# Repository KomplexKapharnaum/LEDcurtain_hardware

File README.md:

# Teensy KxKm Artnet Node Hardware
**Version: V1.5.0**
# Clément SAILLANT pour KomplexKapharnaüm

Ce projet est la partie hardware d'un nœud Artnet basé sur Teensy 4.1 pour contrôler jusqu'a 50 bandes LED. La Teensy 4.1 est un microcontrôleur puissant capable de piloter un grand nombre de LEDs. Ce projet utilise la bibliothèque FastLED et objectFLED pour contrôler les LEDs et la bibliothèque Artnet pour recevoir les données Artnet.

ce repo contient le Schéma et PCB pour la gestion jusqu'à 40 ruban led en artnet (ou autres) avec une teensy 4.1
avec gestion d'alimentation pour économiser l'énergie quand les ruban de led n'affiche rien.

code disponible ici :
https://github.com/KomplexKapharnaum/LEDcurtain/tree/main

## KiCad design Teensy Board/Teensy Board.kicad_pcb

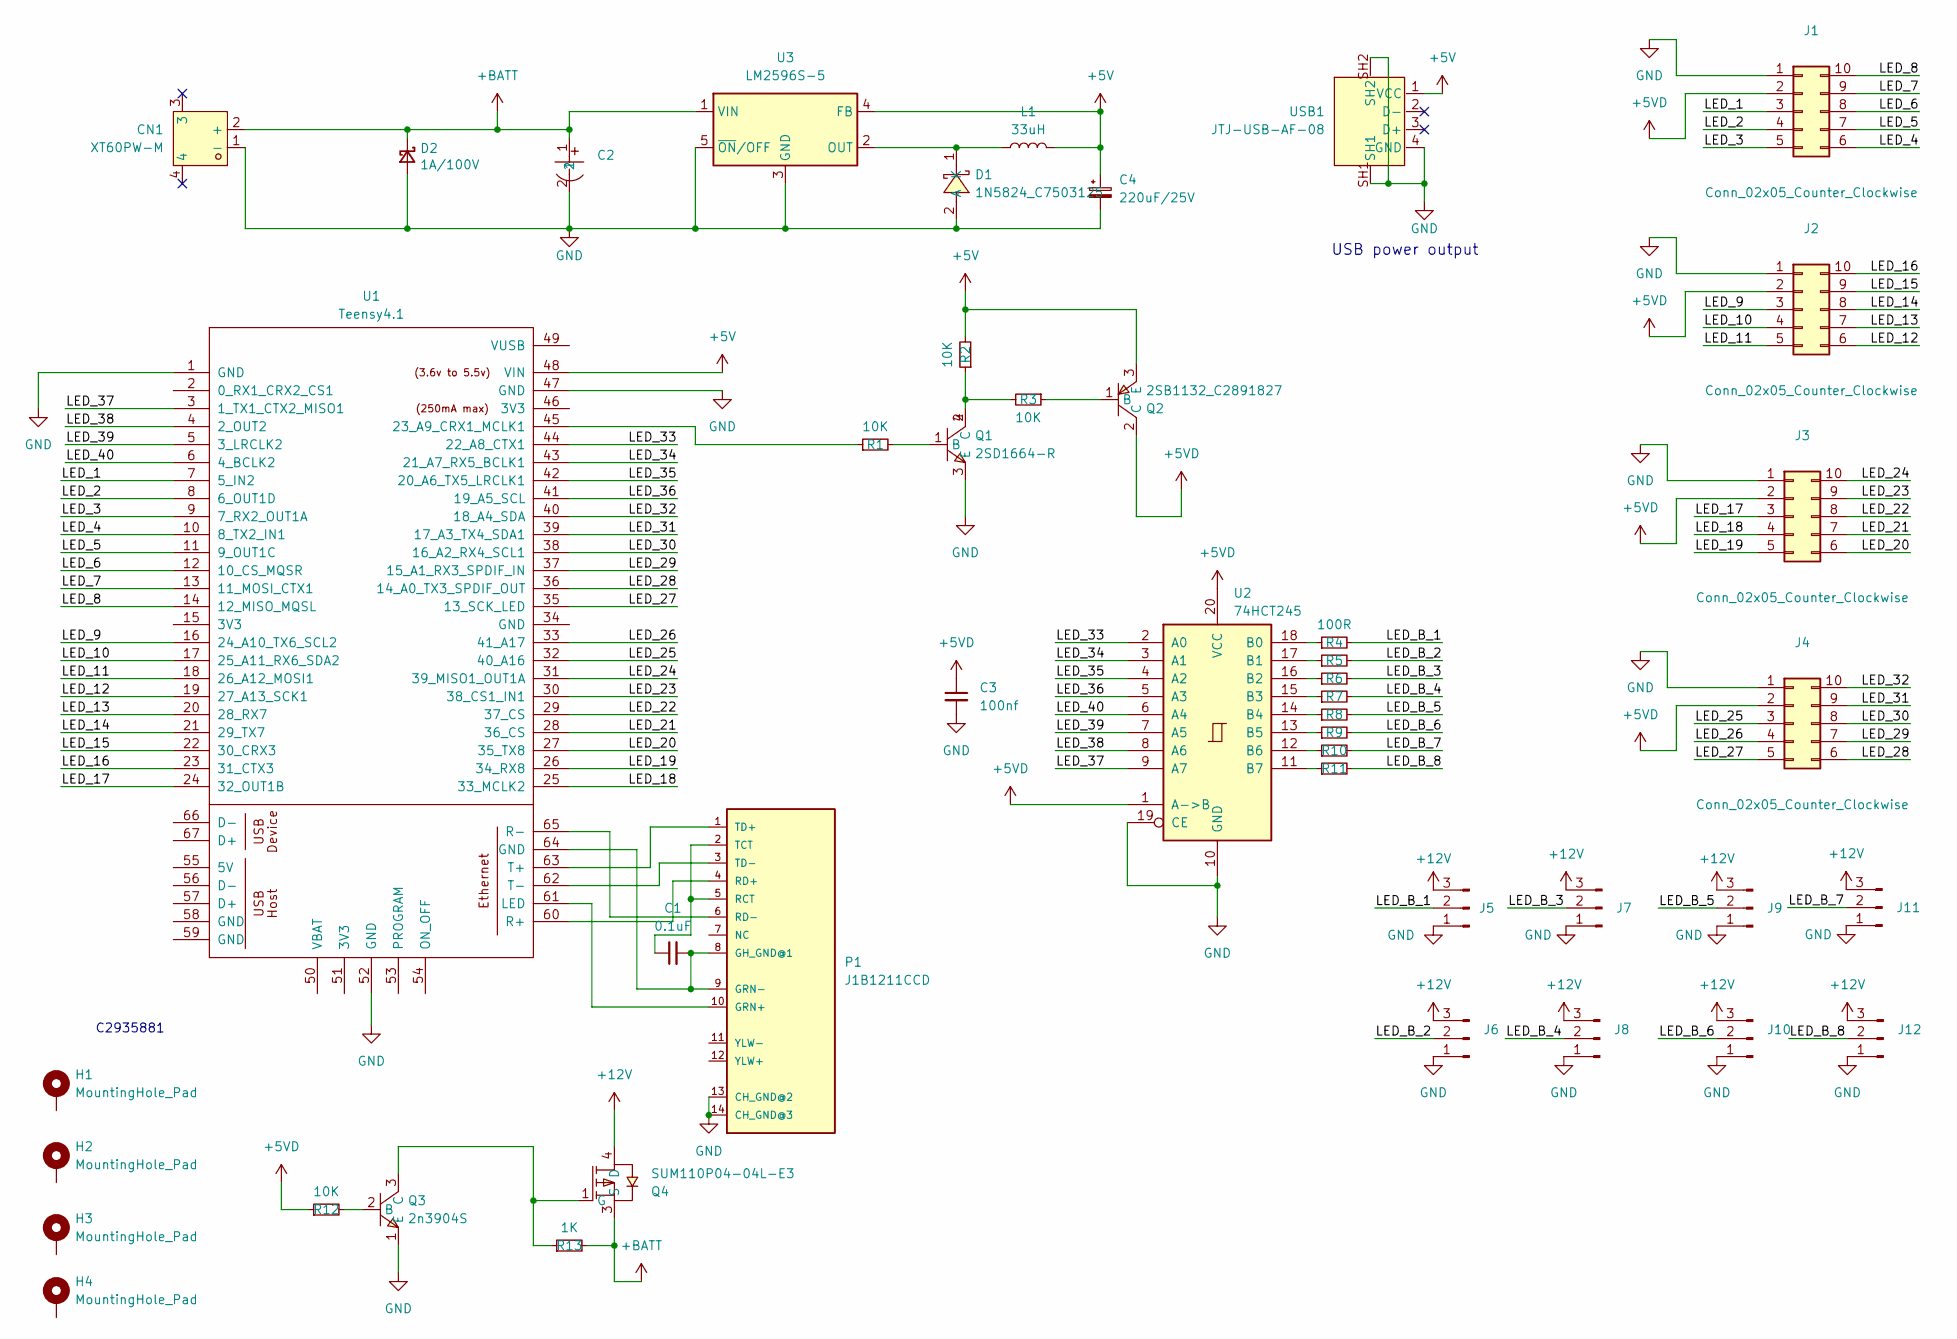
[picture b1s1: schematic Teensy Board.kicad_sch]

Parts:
C1: 0.1uF; CAP-TH_L3.8-W2.5-P2.50-D0.51; LCSC Part C575458
C2: RVT1H221M1010-C3358; CAP-SMD_BD10.0-L10.3-W10.3-LS11.3-FD; LCSC Part C3358
C3: 100nf; C_0805_2012Metric_Pad1.18x1.45mm_HandSolder; LCSC C14663
C4: 220uF/25V; CP_Elec_8x10; LCSC Part C3353
CN1: XT60PW-M; CONN-TH_XT60PW-M; LCSC Part C98732
D1: 1N5824_C7503125; DO-27_BD5.3-L8.4-P12.40-D1.3-RD; LCSC Part C7503125
D2: 1A/100V; D_SMA; LCSC C14996
H1, H2, H3, H4: MountingHole_Pad; MountingHole_3.2mm_M3_DIN965_Pad_TopOnly
J1, J2, J3, J4: Conn_02x05_Counter_Clockwise; IDC-Header_2x05_P2.54mm_Vertical
J5, J6, J7, J8, J9, J10, J11, J12: Conn_01x03_Pin; PinSocket_1x03_P2.54mm_Vertical
L1: 33uH; L_12x12mm_H6mm
P1: J1B1211CCD; RJ45-TH_J1B1211CCD; LCSC Part C910371
Q1: 2SD1664-R; SOT-89-4_L4.5-W2.5-P1.50-LS4.2-BR; LCSC Part C489328
Q2: 2SB1132_C2891827; SOT-89-3_L4.5-W2.5-P1.50-LS4.0-BR; LCSC Part C2891827
Q3: 2n3904S; SOT-23-3_L2.9-W1.3-P1.90-LS2.4-TR; LCSC Part C18536
Q4: SUM110P04-04L-E3; TO-263-2_L10.1-W9.1-P5.08-LS15.2-TL-1; LCSC Part C222440
R1, R2, R3, R12: 10K; R_0603_1608Metric
R4, R5, R6, R7, R8, R9, R10, R11: 100R; R_0603_1608Metric
R13: 1K; R_0603_1608Metric
U1: Teensy4.1; Teensy41; LCSC Part C2935881
U2: 74HCT245; TSSOP-20_4.4x6.5mm_P0.65mm
U3: LM2596S-5; TO-263-5_TabPin3
USB1: JTJ-USB-AF-08; USB-A-TH__USB-AF-90; LCSC Part C2345

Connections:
+5V: C4.1, L1.2, Q2.3 (E), R2.2, U1.48 (VIN), U3.4 (FB), USB1.1 (VCC)
+5VD: C3.1, J1.2, J2.2, J3.2, J4.2, Q2.2 (C), R12.1, U2.1 (A->B), U2.20 (VCC)
+12V: J5.3, J6.3, J7.3, J8.3, J9.3, J10.3, J11.3, J12.3, Q4.4 (D)
+BATT: C2.1, CN1.2 (+), D2.1 (K), Q4.3 (S), R13.2, U3.1 (VIN)
/LED_1: J1.3, U1.7 (5_IN2)
/LED_2: J1.4, U1.8 (6_OUT1D)
/LED_3: J1.5, U1.9 (7_RX2_OUT1A)
/LED_4: J1.6, U1.10 (8_TX2_IN1)
/LED_5: J1.7, U1.11 (9_OUT1C)
/LED_6: J1.8, U1.12 (10_CS_MQSR)
/LED_7: J1.9, U1.13 (11_MOSI_CTX1)
/LED_8: J1.10, U1.14 (12_MISO_MQSL)
/LED_9: J2.3, U1.16 (24_A10_TX6_SCL2)
/LED_10: J2.4, U1.17 (25_A11_RX6_SDA2)
/LED_11: J2.5, U1.18 (26_A12_MOSI1)
/LED_12: J2.6, U1.19 (27_A13_SCK1)
/LED_13: J2.7, U1.20 (28_RX7)
/LED_14: J2.8, U1.21 (29_TX7)
/LED_15: J2.9, U1.22 (30_CRX3)
/LED_16: J2.10, U1.23 (31_CTX3)
/LED_17: J3.3, U1.24 (32_OUT1B)
/LED_18: J3.4, U1.25 (33_MCLK2)
/LED_19: J3.5, U1.26 (34_RX8)
/LED_20: J3.6, U1.27 (35_TX8)
/LED_21: J3.7, U1.28 (36_CS)
/LED_22: J3.8, U1.29 (37_CS)
/LED_23: J3.9, U1.30 (38_CS1_IN1)
/LED_24: J3.10, U1.31 (39_MISO1_OUT1A)
/LED_25: J4.3, U1.32 (40_A16)
/LED_26: J4.4, U1.33 (41_A17)
/LED_27: J4.5, U1.35 (13_SCK_LED)
/LED_28: J4.6, U1.36 (14_A0_TX3_SPDIF_OUT)
/LED_29: J4.7, U1.37 (15_A1_RX3_SPDIF_IN)
/LED_30: J4.8, U1.38 (16_A2_RX4_SCL1)
/LED_31: J4.9, U1.39 (17_A3_TX4_SDA1)
/LED_32: J4.10, U1.40 (18_A4_SDA)
/LED_33: U1.44 (22_A8_CTX1), U2.2 (A0)
/LED_34: U1.43 (21_A7_RX5_BCLK1), U2.3 (A1)
/LED_35: U1.42 (20_A6_TX5_LRCLK1), U2.4 (A2)
/LED_36: U1.41 (19_A5_SCL), U2.5 (A3)
/LED_37: U1.3 (1_TX1_CTX2_MISO1), U2.9 (A7)
/LED_38: U1.4 (2_OUT2), U2.8 (A6)
/LED_39: U1.5 (3_LRCLK2), U2.7 (A5)
/LED_40: U1.6 (4_BCLK2), U2.6 (A4)
/LED_B_1: J5.2, R4.2
/LED_B_2: J6.2, R5.2
/LED_B_3: J7.2, R6.2
/LED_B_4: J8.2, R7.2
/LED_B_5: J9.2, R8.2
/LED_B_6: J10.2, R9.2
/LED_B_7: J11.2, R10.2
/LED_B_8: J12.2, R11.2
GND: C2.2, C3.2, C4.2, CN1.1 (-), D1.2 (A), D2.2 (A), J1.1, J2.1, J3.1, J4.1, J5.1, J6.1, J7.1, J8.1, J9.1, J10.1, J11.1, J12.1, P1.13 (CH_GND@2), P1.14 (CH_GND@3), Q1.3 (E), Q3.1 (E), U1.1 (GND), U1.47 (GND), U1.52 (GND), U2.10 (GND), U2.19 (CE), U3.3 (GND), U3.5 (~ON/OFF), USB1.4 (GND), USB1.SH1, USB1.SH2
unnamed: D1.1 (K), L1.1, U3.2 (OUT)
unnamed: C1.2, P1.8 (GH_GND@1), P1.9 (GRN-), U1.64 (GND)
unnamed: P1.10 (GRN+), U1.61 (LED)
unnamed: C1.1, P1.2 (TCT), P1.5 (RCT)
unnamed: P1.4 (RD+), U1.60 (R+)
unnamed: P1.6 (RD-), U1.65 (R-)
unnamed: P1.1 (TD+), U1.63 (T+)
unnamed: P1.3 (TD-), U1.62 (T-)
unnamed: Q1.1 (B), R1.2
unnamed: Q1.2 (C), Q1.4 (C), R2.1, R3.2
unnamed: Q2.1 (B), R3.1
unnamed: Q3.2 (B), R12.2
unnamed: Q3.3 (C), Q4.1 (G), R13.1
unnamed: R1.1, U1.45 (23_A9_CRX1_MCLK1)
unnamed: R4.1, U2.18 (B0)
unnamed: R5.1, U2.17 (B1)
unnamed: R6.1, U2.16 (B2)
unnamed: R7.1, U2.15 (B3)
unnamed: R8.1, U2.14 (B4)
unnamed: R9.1, U2.13 (B5)
unnamed: R10.1, U2.12 (B6)
unnamed: R11.1, U2.11 (B7)

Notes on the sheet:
C2935881
USB power output

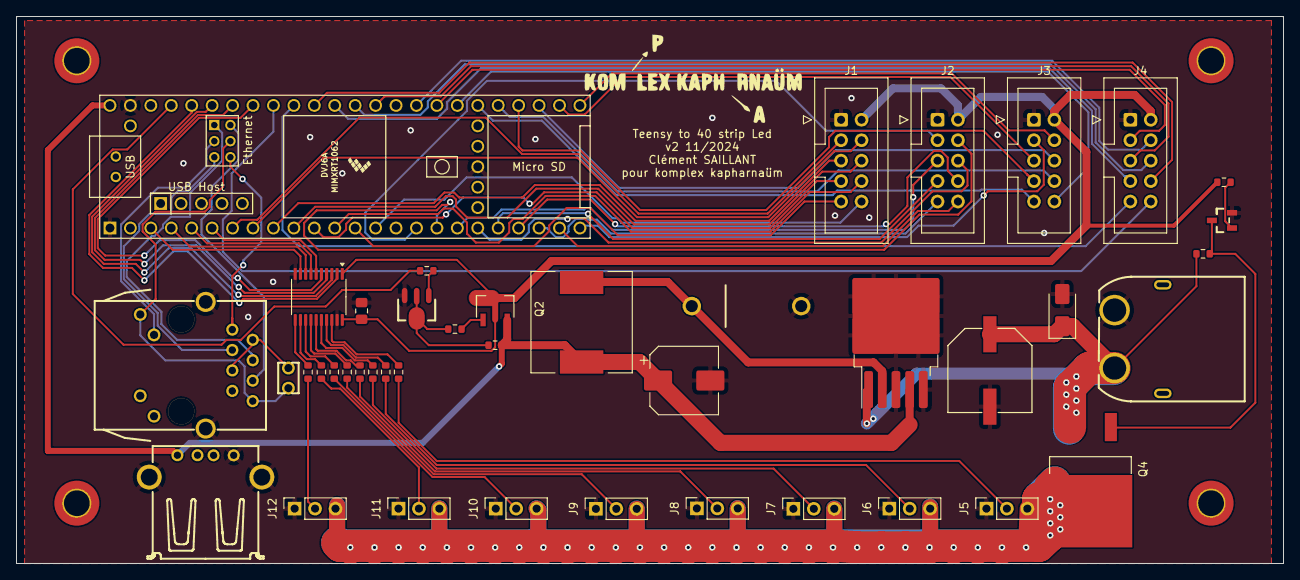
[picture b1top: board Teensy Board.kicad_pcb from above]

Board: 2 copper layers, 157.5 x 68.0 mm, 46 parts (0 on the bottom side), 75 nets.

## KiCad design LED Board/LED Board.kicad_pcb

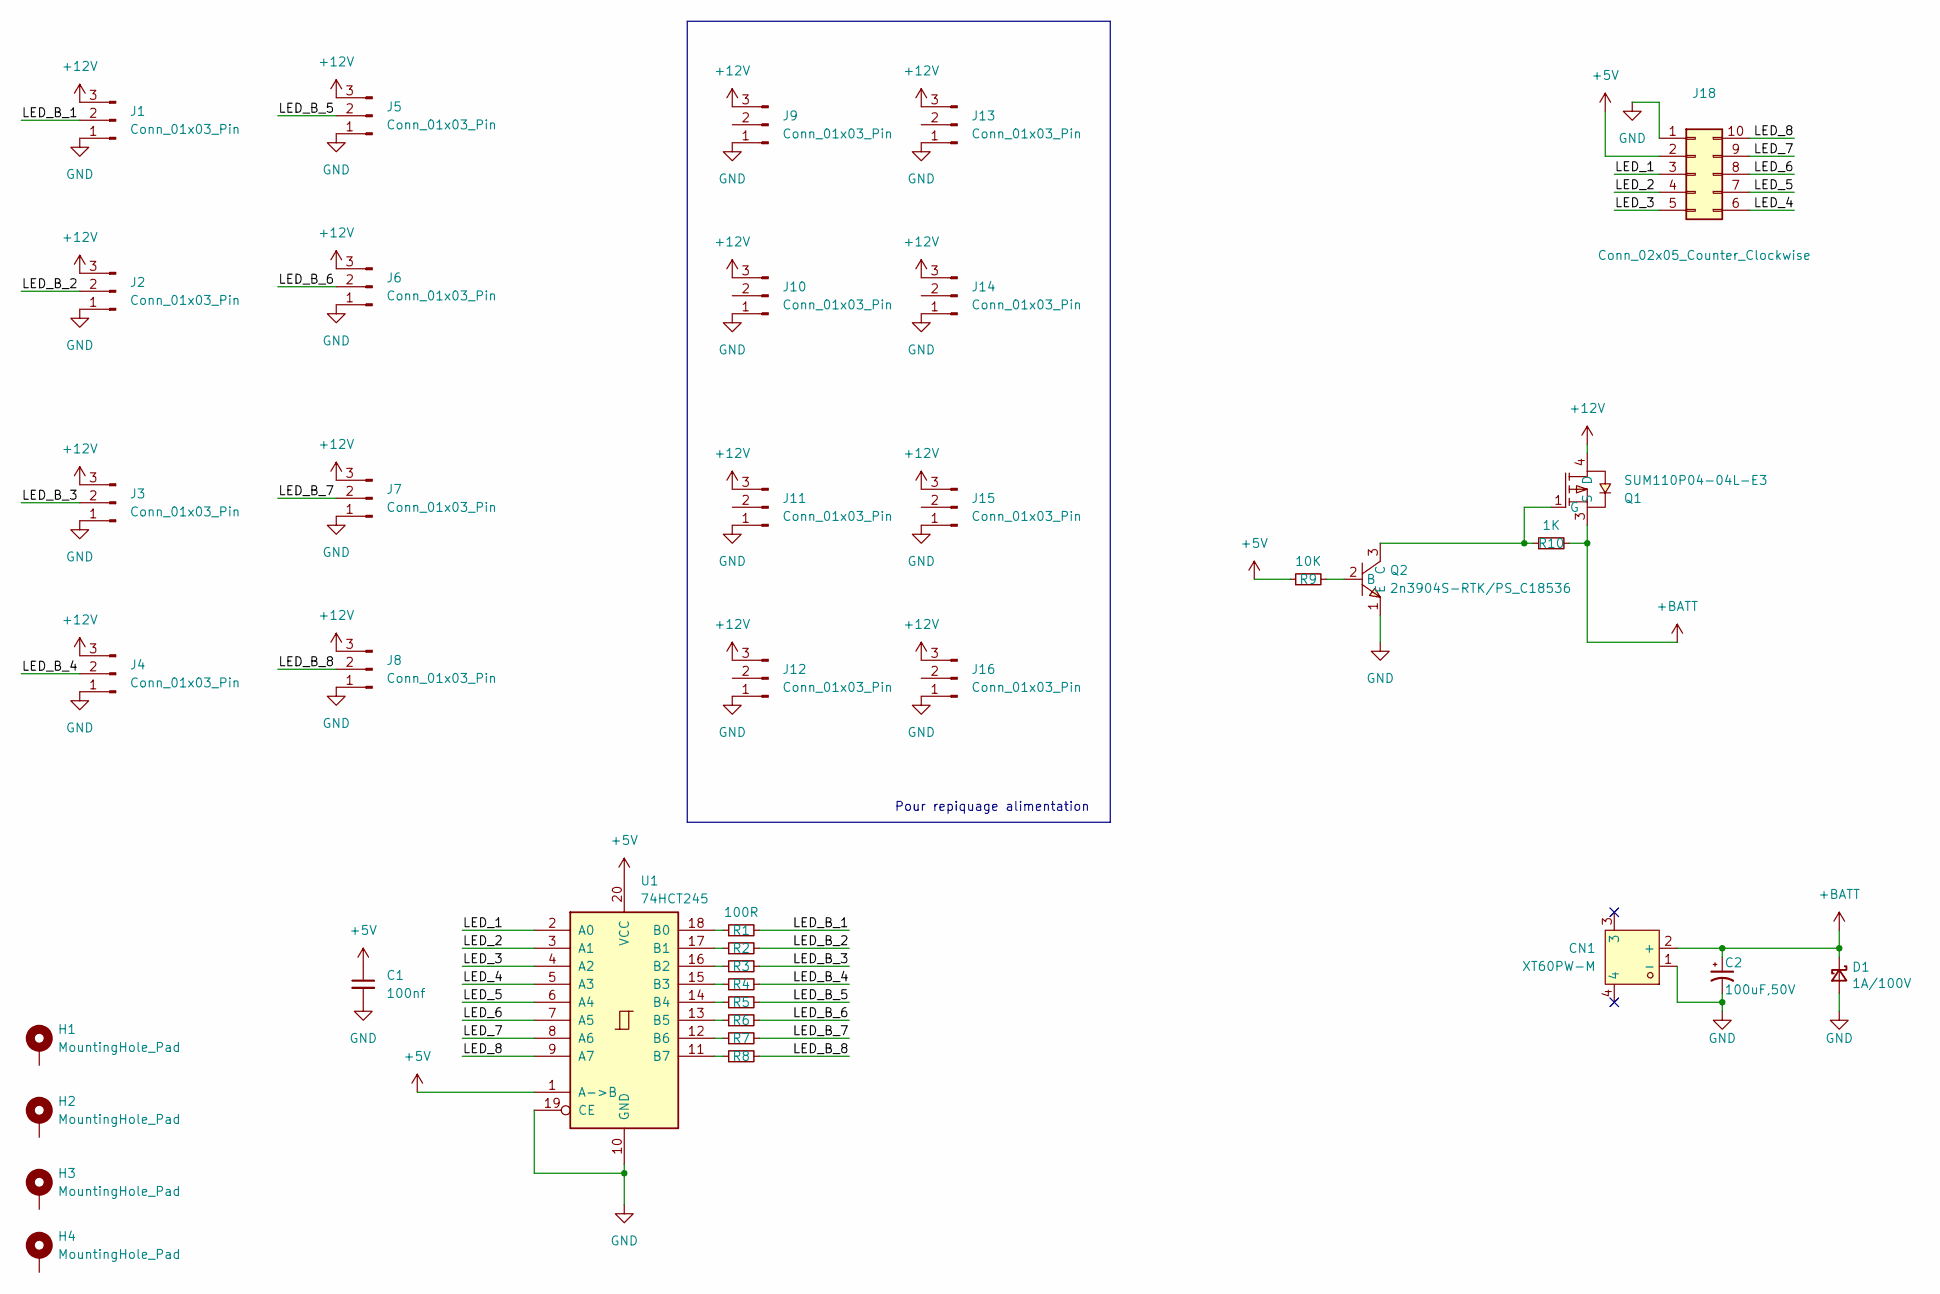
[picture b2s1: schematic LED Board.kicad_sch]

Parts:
C1: 100nf; C_0805_2012Metric_Pad1.18x1.45mm_HandSolder; LCSC C14663
C2: 100uF,50V; CP_Elec_8x10; LCSC C97812
CN1: XT60PW-M; CONN-TH_XT60PW-M; LCSC Part C98732
D1: 1A/100V; D_SMA; LCSC C14996
H1, H2, H3, H4: MountingHole_Pad; MountingHole_3.2mm_M3_DIN965_Pad_TopOnly
J1, J2, J3, J4, J5, J6, J7, J8: Conn_01x03_Pin; PinSocket_1x03_P2.54mm_Horizontal
J9, J10, J11, J12, J13, J14, J15, J16: Conn_01x03_Pin; PinSocket_1x03_P2.54mm_Vertical
J18: Conn_02x05_Counter_Clockwise; IDC-Header_2x05_P2.54mm_Vertical
Q1: SUM110P04-04L-E3; TO-263-2_L10.1-W9.1-P5.08-LS15.2-TL-1; LCSC Part C222440
Q2: 2n3904S-RTK/PS_C18536; SOT-23-3_L2.9-W1.3-P1.90-LS2.4-TR; LCSC Part C18536
R1, R2, R3, R4, R5, R6, R7, R8: 100R; R_0603_1608Metric
R9: 10K; R_0603_1608Metric
R10: 1K; R_0603_1608Metric
U1: 74HCT245; TSSOP-20_4.4x6.5mm_P0.65mm

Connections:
+5V: C1.1, J18.2, R9.1, U1.1 (A->B), U1.20 (VCC)
+12V: J1.3, J2.3, J3.3, J4.3, J5.3, J6.3, J7.3, J8.3, J9.3, J10.3, J11.3, J12.3, J13.3, J14.3, J15.3, J16.3, Q1.4 (D)
+BATT: C2.1, CN1.2 (+), D1.1 (K), Q1.3 (S), R10.2
/LED_1: J18.3, U1.2 (A0)
/LED_2: J18.4, U1.3 (A1)
/LED_3: J18.5, U1.4 (A2)
/LED_4: J18.6, U1.5 (A3)
/LED_5: J18.7, U1.6 (A4)
/LED_6: J18.8, U1.7 (A5)
/LED_7: J18.9, U1.8 (A6)
/LED_8: J18.10, U1.9 (A7)
/LED_B_1: J1.2, R1.2
/LED_B_2: J2.2, R2.2
/LED_B_3: J3.2, R3.2
/LED_B_4: J4.2, R4.2
/LED_B_5: J5.2, R5.2
/LED_B_6: J6.2, R6.2
/LED_B_7: J7.2, R7.2
/LED_B_8: J8.2, R8.2
GND: C1.2, C2.2, CN1.1 (-), D1.2 (A), J1.1, J2.1, J3.1, J4.1, J5.1, J6.1, J7.1, J8.1, J9.1, J10.1, J11.1, J12.1, J13.1, J14.1, J15.1, J16.1, J18.1, Q2.1 (E), U1.10 (GND), U1.19 (CE)
unnamed: Q1.1 (G), Q2.3 (C), R10.1
unnamed: Q2.2 (B), R9.2
unnamed: R1.1, U1.18 (B0)
unnamed: R2.1, U1.17 (B1)
unnamed: R3.1, U1.16 (B2)
unnamed: R4.1, U1.15 (B3)
unnamed: R5.1, U1.14 (B4)
unnamed: R6.1, U1.13 (B5)
unnamed: R7.1, U1.12 (B6)
unnamed: R8.1, U1.11 (B7)

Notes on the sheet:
Pour repiquage alimentation

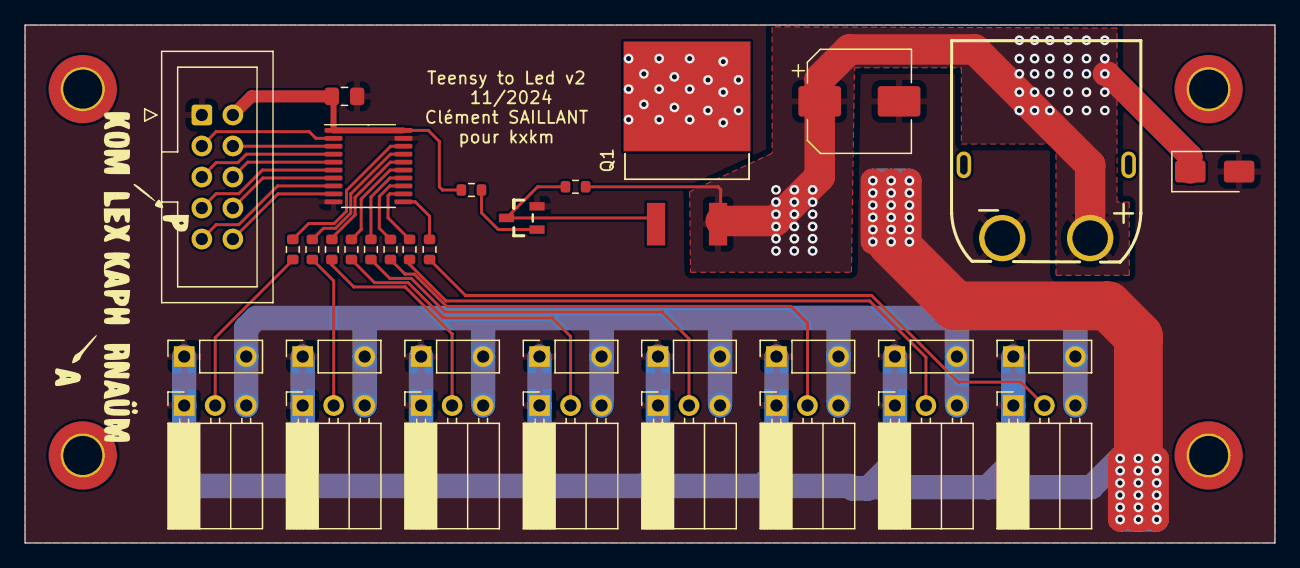
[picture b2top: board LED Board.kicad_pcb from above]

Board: 2 copper layers, 102.4 x 42.4 mm, 38 parts (0 on the bottom side), 30 nets.

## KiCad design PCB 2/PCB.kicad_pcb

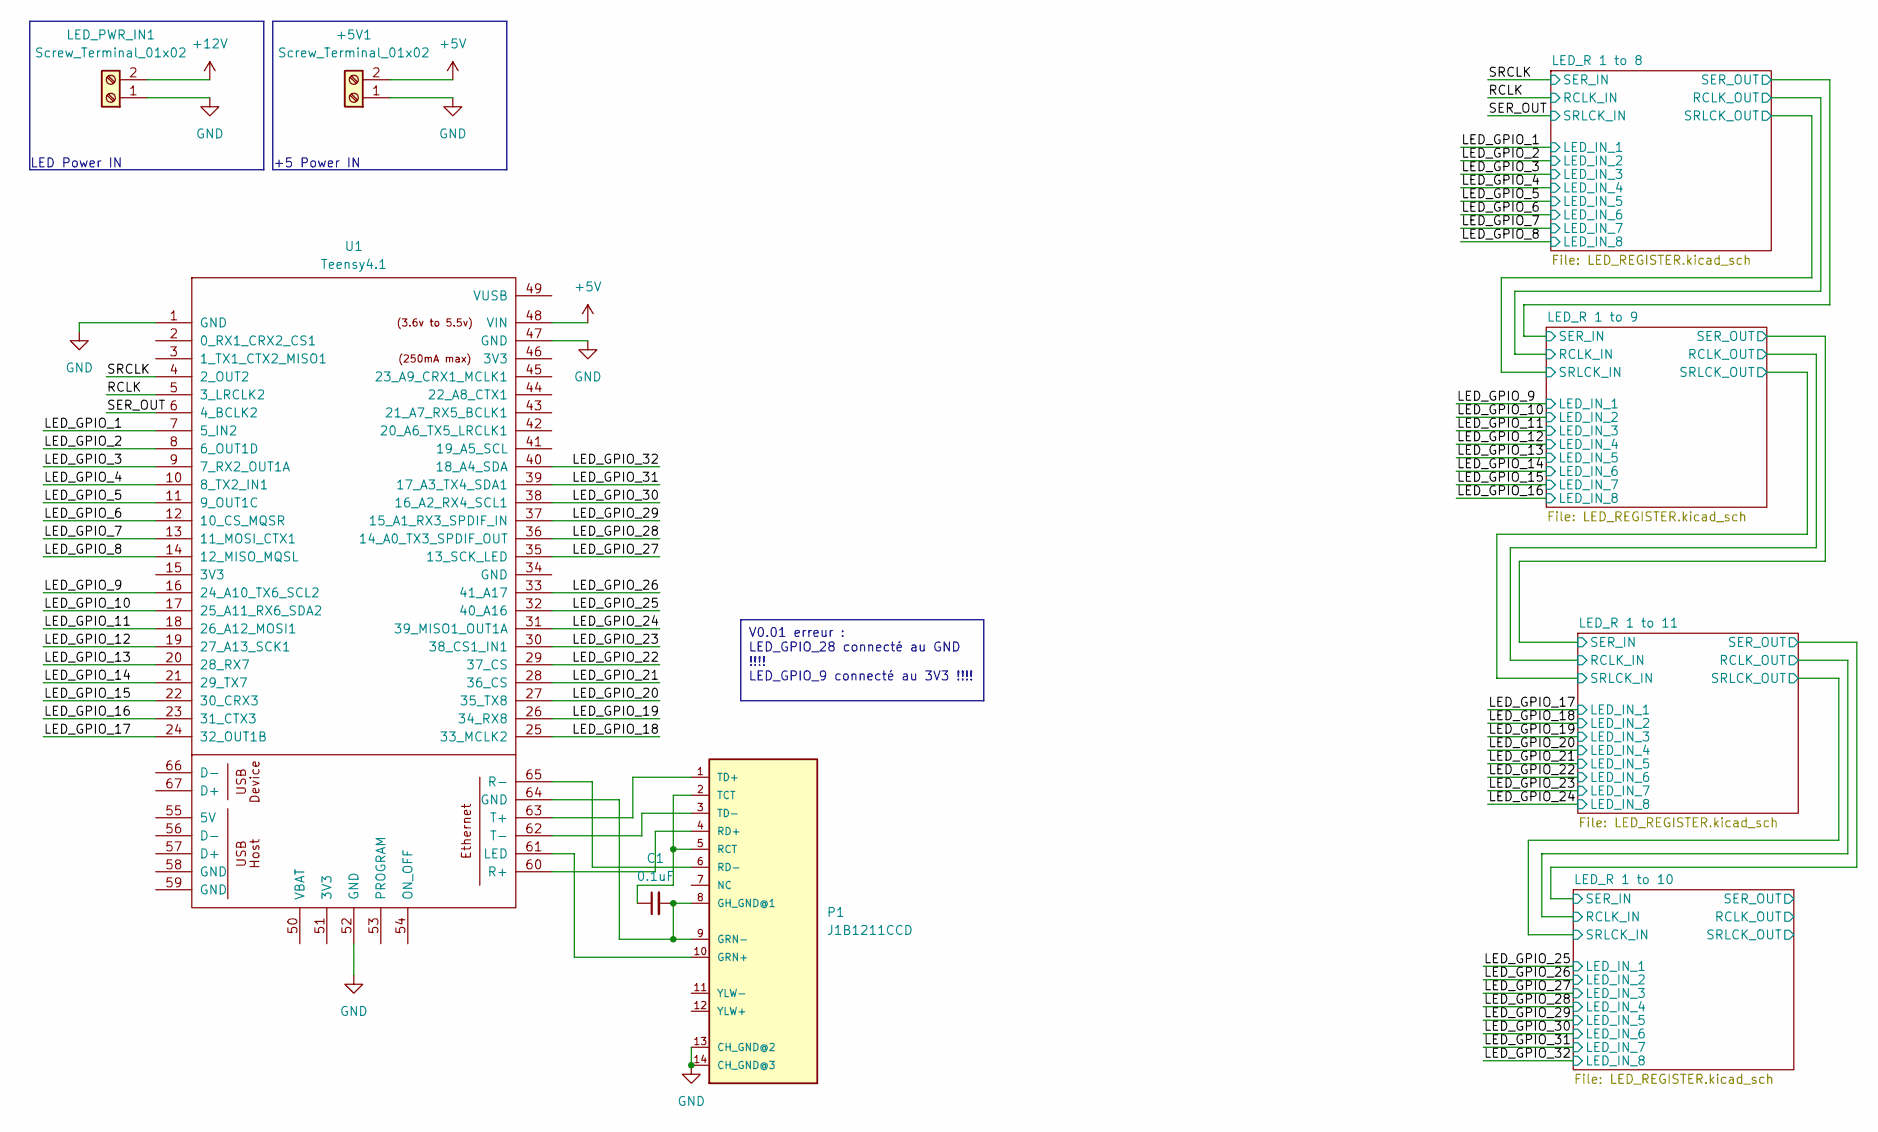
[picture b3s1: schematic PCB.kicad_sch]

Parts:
+5V1: Screw_Terminal_01x02; Wago_734-162_1x02_P3.50mm_Horizontal
C1: 0.1uF; C_Disc_D3.0mm_W1.6mm_P2.50mm
LED_PWR_IN1: Screw_Terminal_01x02; SolderWire-2.5sqmm_1x02_P8.8mm_D2.4mm_OD4.4mm
P1: J1B1211CCD
U1: Teensy4.1; Teensy41

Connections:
+5V: +5V1.2, U1.48 (VIN); also elsewhere on the board
+12V: LED_PWR_IN1.2; also elsewhere on the board
/LED_GPIO_1: U1.7 (5_IN2); also elsewhere on the board
/LED_GPIO_2: U1.8 (6_OUT1D); also elsewhere on the board
/LED_GPIO_3: U1.9 (7_RX2_OUT1A); also elsewhere on the board
/LED_GPIO_4: U1.10 (8_TX2_IN1); also elsewhere on the board
/LED_GPIO_5: U1.11 (9_OUT1C); also elsewhere on the board
/LED_GPIO_6: U1.12 (10_CS_MQSR); also elsewhere on the board
/LED_GPIO_7: U1.13 (11_MOSI_CTX1); also elsewhere on the board
/LED_GPIO_8: U1.14 (12_MISO_MQSL); also elsewhere on the board
/LED_GPIO_9: U1.15 (3V3); also elsewhere on the board
/LED_GPIO_10: U1.16 (24_A10_TX6_SCL2); also elsewhere on the board
/LED_GPIO_11: U1.17 (25_A11_RX6_SDA2); also elsewhere on the board
/LED_GPIO_12: U1.18 (26_A12_MOSI1); also elsewhere on the board
/LED_GPIO_13: U1.19 (27_A13_SCK1); also elsewhere on the board
/LED_GPIO_14: U1.20 (28_RX7); also elsewhere on the board
/LED_GPIO_15: U1.21 (29_TX7); also elsewhere on the board
/LED_GPIO_16: U1.22 (30_CRX3); also elsewhere on the board
/LED_GPIO_17: U1.23 (31_CTX3); also elsewhere on the board
/LED_GPIO_18: U1.24 (32_OUT1B); also elsewhere on the board
/LED_GPIO_19: U1.25 (33_MCLK2); also elsewhere on the board
/LED_GPIO_20: U1.26 (34_RX8); also elsewhere on the board
/LED_GPIO_21: U1.27 (35_TX8); also elsewhere on the board
/LED_GPIO_22: U1.28 (36_CS); also elsewhere on the board
/LED_GPIO_23: U1.29 (37_CS); also elsewhere on the board
/LED_GPIO_24: U1.30 (38_CS1_IN1); also elsewhere on the board
/LED_GPIO_25: U1.31 (39_MISO1_OUT1A); also elsewhere on the board
/LED_GPIO_26: U1.32 (40_A16); also elsewhere on the board
/LED_GPIO_27: U1.33 (41_A17); also elsewhere on the board
/LED_GPIO_28: U1.34 (GND); also elsewhere on the board
/LED_GPIO_29: U1.36 (14_A0_TX3_SPDIF_OUT); also elsewhere on the board
/LED_GPIO_30: U1.37 (15_A1_RX3_SPDIF_IN); also elsewhere on the board
/LED_GPIO_31: U1.38 (16_A2_RX4_SCL1); also elsewhere on the board
/LED_GPIO_32: U1.39 (17_A3_TX4_SDA1); also elsewhere on the board
/RCLK: U1.5 (3_LRCLK2); also elsewhere on the board
/SER_OUT: U1.6 (4_BCLK2); also elsewhere on the board
/SRCLK: U1.4 (2_OUT2); also elsewhere on the board
GND: +5V1.1, LED_PWR_IN1.1, P1.13 (CH_GND@2), P1.14 (CH_GND@3), U1.1 (GND), U1.47 (GND), U1.52 (GND); also elsewhere on the board
unnamed: C1.2, P1.8 (GH_GND@1), P1.9 (GRN-), U1.64 (GND)
unnamed: P1.10 (GRN+), U1.61 (LED)
unnamed: C1.1, P1.2 (TCT), P1.5 (RCT)
unnamed: P1.4 (RD+), U1.60 (R+)
unnamed: P1.6 (RD-), U1.65 (R-)
unnamed: P1.1 (TD+), U1.63 (T+)
unnamed: P1.3 (TD-), U1.62 (T-)

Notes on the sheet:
V0.01 erreur : LED_GPIO_28 connecté au GND !!!! LED_GPIO_9 connecté au 3V3 !!!!
+5 Power IN
LED Power IN

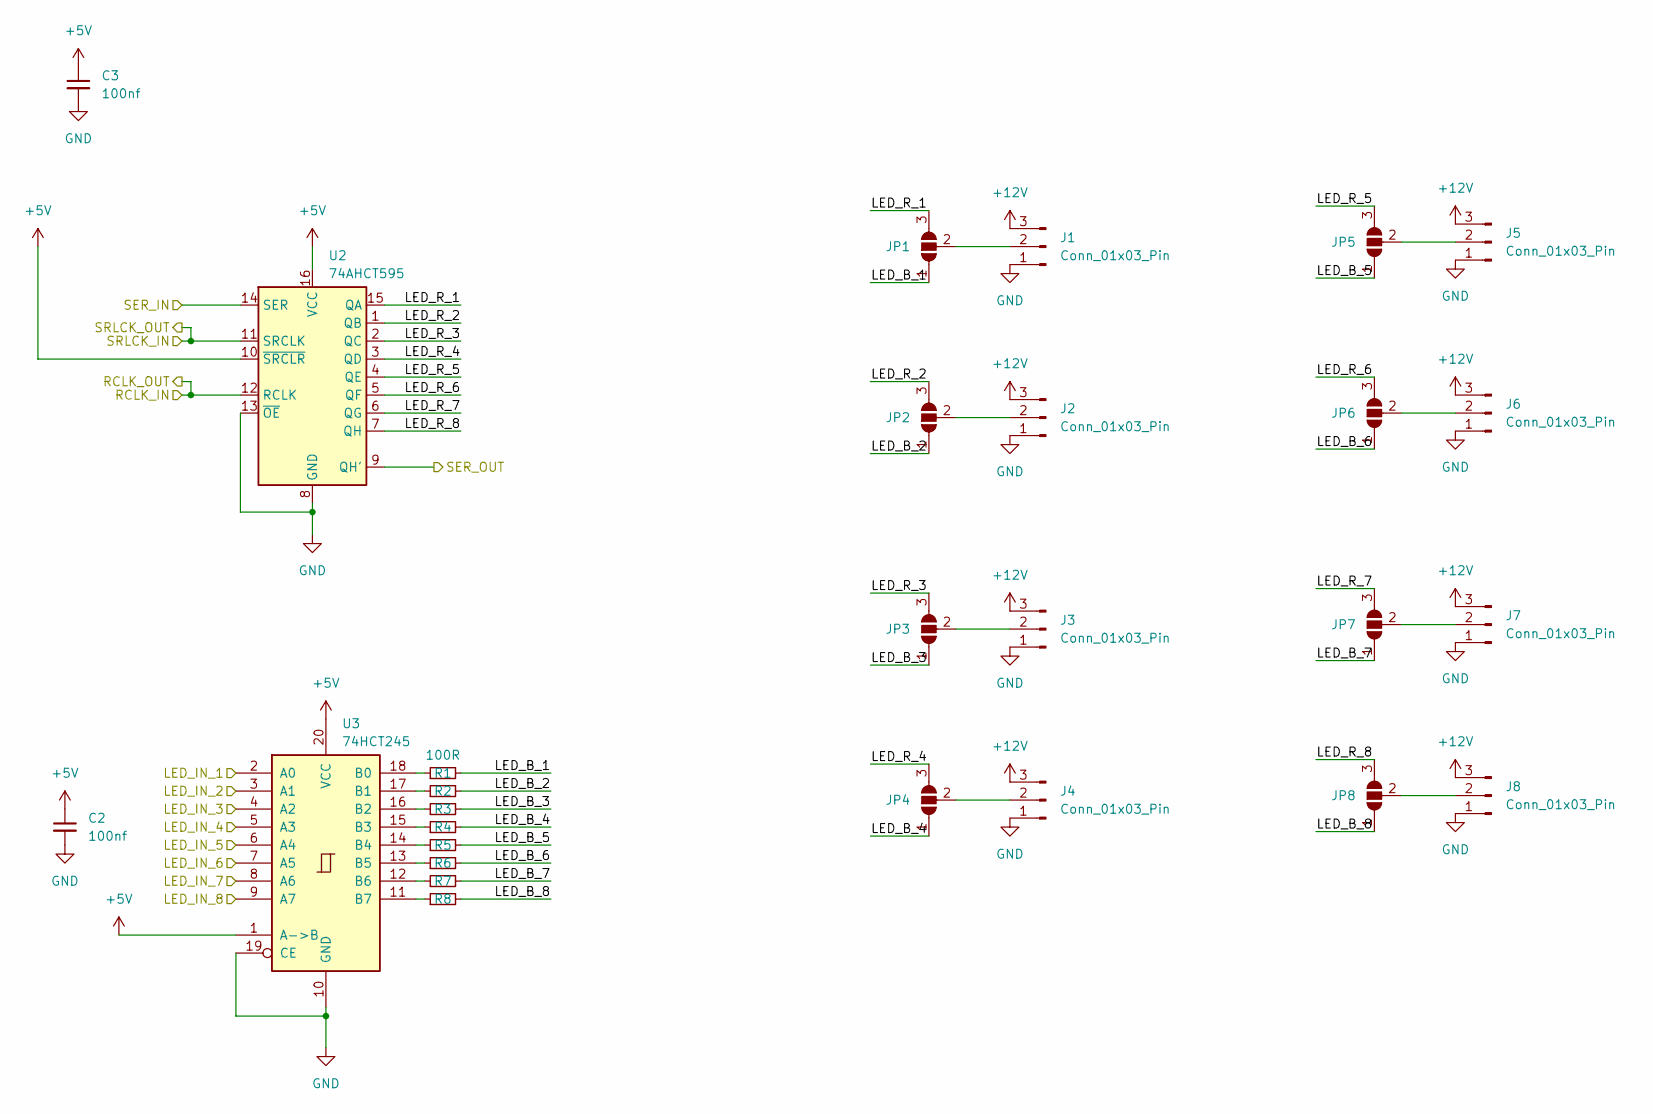
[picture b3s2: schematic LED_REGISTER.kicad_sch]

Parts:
C2, C3: 100nf; C_0805_2012Metric_Pad1.18x1.45mm_HandSolder; LCSC C14663
J1, J2, J3, J4, J5, J6, J7, J8: Conn_01x03_Pin; SolderWire-2.5sqmm_1x03_P7.2mm_D2.4mm_OD3.6mm
JP1, JP2, JP3, JP4, JP5, JP6, JP7, JP8: SolderJumper_3_Open; SolderJumper-3_P1.3mm_Open_RoundedPad1.0x1.5mm_NumberLabels
R1, R2, R3, R4, R5, R6, R7, R8: 100R; R_0201_0603Metric
U2: 74AHCT595; TSSOP-16_4.4x5mm_P0.65mm
U3: 74HCT245; TSSOP-20_4.4x6.5mm_P0.65mm

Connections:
+5V: C2.1, C3.1, U2.10 (~SRCLR), U2.16 (VCC), U3.1 (A->B), U3.20 (VCC); also elsewhere on the board
+12V: J1.3, J2.3, J3.3, J4.3, J5.3, J6.3, J7.3, J8.3; also elsewhere on the board
/LED_GPIO_1: U3.2 (A0); also elsewhere on the board
/LED_GPIO_2: U3.3 (A1); also elsewhere on the board
/LED_GPIO_3: U3.4 (A2); also elsewhere on the board
/LED_GPIO_4: U3.5 (A3); also elsewhere on the board
/LED_GPIO_5: U3.6 (A4); also elsewhere on the board
/LED_GPIO_6: U3.7 (A5); also elsewhere on the board
/LED_GPIO_7: U3.8 (A6); also elsewhere on the board
/LED_GPIO_8: U3.9 (A7); also elsewhere on the board
/LED_R 1 to 8/LED_B_1: JP1.1 (A), R1.2
/LED_R 1 to 8/LED_B_2: JP2.1 (A), R2.2
/LED_R 1 to 8/LED_B_3: JP3.1 (A), R3.2
/LED_R 1 to 8/LED_B_4: JP4.1 (A), R4.2
/LED_R 1 to 8/LED_B_5: JP5.1 (A), R5.2
/LED_R 1 to 8/LED_B_6: JP6.1 (A), R6.2
/LED_R 1 to 8/LED_B_7: JP7.1 (A), R7.2
/LED_R 1 to 8/LED_B_8: JP8.1 (A), R8.2
/LED_R 1 to 8/LED_R_1: JP1.3 (B), U2.15 (QA)
/LED_R 1 to 8/LED_R_2: JP2.3 (B), U2.1 (QB)
/LED_R 1 to 8/LED_R_3: JP3.3 (B), U2.2 (QC)
/LED_R 1 to 8/LED_R_4: JP4.3 (B), U2.3 (QD)
/LED_R 1 to 8/LED_R_5: JP5.3 (B), U2.4 (QE)
/LED_R 1 to 8/LED_R_6: JP6.3 (B), U2.5 (QF)
/LED_R 1 to 8/LED_R_7: JP7.3 (B), U2.6 (QG)
/LED_R 1 to 8/LED_R_8: JP8.3 (B), U2.7 (QH)
/LED_R 1 to 8/SER_OUT: U2.9 (QH'); also elsewhere on the board
/RCLK: U2.12 (RCLK); also elsewhere on the board
/SER_OUT: U2.11 (SRCLK); also elsewhere on the board
/SRCLK: U2.14 (SER); also elsewhere on the board
GND: C2.2, C3.2, J1.1, J2.1, J3.1, J4.1, J5.1, J6.1, J7.1, J8.1, U2.8 (GND), U2.13 (~OE), U3.10 (GND), U3.19 (CE); also elsewhere on the board
unnamed: J1.2, JP1.2 (C)
unnamed: J2.2, JP2.2 (C)
unnamed: J3.2, JP3.2 (C)
unnamed: J4.2, JP4.2 (C)
unnamed: J5.2, JP5.2 (C)
unnamed: J6.2, JP6.2 (C)
unnamed: J7.2, JP7.2 (C)
unnamed: J8.2, JP8.2 (C)
unnamed: R1.1, U3.18 (B0)
unnamed: R2.1, U3.17 (B1)
unnamed: R3.1, U3.16 (B2)
unnamed: R4.1, U3.15 (B3)
unnamed: R5.1, U3.14 (B4)
unnamed: R6.1, U3.13 (B5)
unnamed: R7.1, U3.12 (B6)
unnamed: R8.1, U3.11 (B7)

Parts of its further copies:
C4, C5, C6, C7, C8, C9: 100nf; C_0805_2012Metric_Pad1.18x1.45mm_HandSolder; LCSC C14663
J9, J10, J11, J12, J13, J14, J15, J16, J17, J18, J19, J20, J21, J22, J23, J24, J25, J26, J27, J28, J29, J30, J31, J32: Conn_01x03_Pin; SolderWire-2.5sqmm_1x03_P7.2mm_D2.4mm_OD3.6mm
JP9, JP10, JP11, JP12, JP13, JP14, JP15, JP16, JP17, JP18, JP19, JP20, JP21, JP22, JP23, JP24, JP25, JP26, JP27, JP28, JP29, JP30, JP31, JP32: SolderJumper_3_Open; SolderJumper-3_P1.3mm_Open_RoundedPad1.0x1.5mm_NumberLabels
R9, R10, R11, R12, R13, R14, R15, R16, R17, R18, R19, R20, R21, R22, R23, R24, R25, R26, R27, R28, R29, R30, R31, R32: 100R; R_0201_0603Metric
U4, U6, U8: 74AHCT595; TSSOP-16_4.4x5mm_P0.65mm
U5, U7, U9: 74HCT245; TSSOP-20_4.4x6.5mm_P0.65mm

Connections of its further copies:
+5V: C4.1, C5.1, C6.1, C7.1, C8.1, C9.1, U4.10 (~SRCLR), U4.16 (VCC), U5.1 (A->B), U5.20 (VCC), U6.10 (~SRCLR), U6.16 (VCC), U7.1 (A->B), U7.20 (VCC), U8.10 (~SRCLR), U8.16 (VCC), U9.1 (A->B), U9.20 (VCC); also elsewhere on the board
+12V: J9.3, J10.3, J11.3, J12.3, J13.3, J14.3, J15.3, J16.3, J17.3, J18.3, J19.3, J20.3, J21.3, J22.3, J23.3, J24.3, J25.3, J26.3, J27.3, J28.3, J29.3, J30.3, J31.3, J32.3; also elsewhere on the board
/LED_GPIO_9: U5.2 (A0); also elsewhere on the board
/LED_GPIO_10: U5.3 (A1); also elsewhere on the board
/LED_GPIO_11: U5.4 (A2); also elsewhere on the board
/LED_GPIO_12: U5.5 (A3); also elsewhere on the board
/LED_GPIO_13: U5.6 (A4); also elsewhere on the board
/LED_GPIO_14: U5.7 (A5); also elsewhere on the board
/LED_GPIO_15: U5.8 (A6); also elsewhere on the board
/LED_GPIO_16: U5.9 (A7); also elsewhere on the board
/LED_GPIO_17: U7.2 (A0); also elsewhere on the board
/LED_GPIO_18: U7.3 (A1); also elsewhere on the board
/LED_GPIO_19: U7.4 (A2); also elsewhere on the board
/LED_GPIO_20: U7.5 (A3); also elsewhere on the board
/LED_GPIO_21: U7.6 (A4); also elsewhere on the board
/LED_GPIO_22: U7.7 (A5); also elsewhere on the board
/LED_GPIO_23: U7.8 (A6); also elsewhere on the board
/LED_GPIO_24: U7.9 (A7); also elsewhere on the board
/LED_GPIO_25: U9.2 (A0); also elsewhere on the board
/LED_GPIO_26: U9.3 (A1); also elsewhere on the board
/LED_GPIO_27: U9.4 (A2); also elsewhere on the board
/LED_GPIO_28: U9.5 (A3); also elsewhere on the board
/LED_GPIO_29: U9.6 (A4); also elsewhere on the board
/LED_GPIO_30: U9.7 (A5); also elsewhere on the board
/LED_GPIO_31: U9.8 (A6); also elsewhere on the board
/LED_GPIO_32: U9.9 (A7); also elsewhere on the board
/LED_R 1 to 8/SER_OUT: U4.14 (SER); also elsewhere on the board
/LED_R 1 to 9/LED_B_1: JP9.1 (A), R9.2
/LED_R 1 to 9/LED_B_2: JP10.1 (A), R10.2
/LED_R 1 to 9/LED_B_3: JP11.1 (A), R11.2
/LED_R 1 to 9/LED_B_4: JP12.1 (A), R12.2
/LED_R 1 to 9/LED_B_5: JP13.1 (A), R13.2
/LED_R 1 to 9/LED_B_6: JP14.1 (A), R14.2
/LED_R 1 to 9/LED_B_7: JP15.1 (A), R15.2
/LED_R 1 to 9/LED_B_8: JP16.1 (A), R16.2
/LED_R 1 to 9/LED_R_1: JP9.3 (B), U4.15 (QA)
/LED_R 1 to 9/LED_R_2: JP10.3 (B), U4.1 (QB)
/LED_R 1 to 9/LED_R_3: JP11.3 (B), U4.2 (QC)
/LED_R 1 to 9/LED_R_4: JP12.3 (B), U4.3 (QD)
/LED_R 1 to 9/LED_R_5: JP13.3 (B), U4.4 (QE)
/LED_R 1 to 9/LED_R_6: JP14.3 (B), U4.5 (QF)
/LED_R 1 to 9/LED_R_7: JP15.3 (B), U4.6 (QG)
/LED_R 1 to 9/LED_R_8: JP16.3 (B), U4.7 (QH)
/LED_R 1 to 10/LED_B_1: JP25.1 (A), R25.2
/LED_R 1 to 10/LED_B_2: JP26.1 (A), R26.2
/LED_R 1 to 10/LED_B_3: JP27.1 (A), R27.2
/LED_R 1 to 10/LED_B_4: JP28.1 (A), R28.2
/LED_R 1 to 10/LED_B_5: JP29.1 (A), R29.2
/LED_R 1 to 10/LED_B_6: JP30.1 (A), R30.2
/LED_R 1 to 10/LED_B_7: JP31.1 (A), R31.2
/LED_R 1 to 10/LED_B_8: JP32.1 (A), R32.2
/LED_R 1 to 10/LED_R_1: JP25.3 (B), U8.15 (QA)
/LED_R 1 to 10/LED_R_2: JP26.3 (B), U8.1 (QB)
/LED_R 1 to 10/LED_R_3: JP27.3 (B), U8.2 (QC)
/LED_R 1 to 10/LED_R_4: JP28.3 (B), U8.3 (QD)
/LED_R 1 to 10/LED_R_5: JP29.3 (B), U8.4 (QE)
/LED_R 1 to 10/LED_R_6: JP30.3 (B), U8.5 (QF)
/LED_R 1 to 10/LED_R_7: JP31.3 (B), U8.6 (QG)
/LED_R 1 to 10/LED_R_8: JP32.3 (B), U8.7 (QH)
/LED_R 1 to 10/SER_IN: U6.9 (QH'), U8.14 (SER)
/LED_R 1 to 10/SER_OUT: U8.9 (QH')
/LED_R 1 to 11/LED_B_1: JP17.1 (A), R17.2
/LED_R 1 to 11/LED_B_2: JP18.1 (A), R18.2
/LED_R 1 to 11/LED_B_3: JP19.1 (A), R19.2
/LED_R 1 to 11/LED_B_4: JP20.1 (A), R20.2
/LED_R 1 to 11/LED_B_5: JP21.1 (A), R21.2
/LED_R 1 to 11/LED_B_6: JP22.1 (A), R22.2
/LED_R 1 to 11/LED_B_7: JP23.1 (A), R23.2
/LED_R 1 to 11/LED_B_8: JP24.1 (A), R24.2
/LED_R 1 to 11/LED_R_1: JP17.3 (B), U6.15 (QA)
/LED_R 1 to 11/LED_R_2: JP18.3 (B), U6.1 (QB)
/LED_R 1 to 11/LED_R_3: JP19.3 (B), U6.2 (QC)
/LED_R 1 to 11/LED_R_4: JP20.3 (B), U6.3 (QD)
/LED_R 1 to 11/LED_R_5: JP21.3 (B), U6.4 (QE)
/LED_R 1 to 11/LED_R_6: JP22.3 (B), U6.5 (QF)
/LED_R 1 to 11/LED_R_7: JP23.3 (B), U6.6 (QG)
/LED_R 1 to 11/LED_R_8: JP24.3 (B), U6.7 (QH)
/LED_R 1 to 11/SER_IN: U4.9 (QH'), U6.14 (SER)
/RCLK: U4.12 (RCLK), U6.12 (RCLK), U8.12 (RCLK); also elsewhere on the board
/SER_OUT: U4.11 (SRCLK), U6.11 (SRCLK), U8.11 (SRCLK); also elsewhere on the board
GND: C4.2, C5.2, C6.2, C7.2, C8.2, C9.2, J9.1, J10.1, J11.1, J12.1, J13.1, J14.1, J15.1, J16.1, J17.1, J18.1, J19.1, J20.1, J21.1, J22.1, J23.1, J24.1, J25.1, J26.1, J27.1, J28.1, J29.1, J30.1, J31.1, J32.1, U4.8 (GND), U4.13 (~OE), U5.10 (GND), U5.19 (CE), U6.8 (GND), U6.13 (~OE), U7.10 (GND), U7.19 (CE), U8.8 (GND), U8.13 (~OE), U9.10 (GND), U9.19 (CE); also elsewhere on the board
unnamed: J9.2, JP9.2 (C)
unnamed: J10.2, JP10.2 (C)
unnamed: J11.2, JP11.2 (C)
unnamed: J12.2, JP12.2 (C)
unnamed: J13.2, JP13.2 (C)
unnamed: J14.2, JP14.2 (C)
unnamed: J15.2, JP15.2 (C)
unnamed: J16.2, JP16.2 (C)
unnamed: J17.2, JP17.2 (C)
unnamed: J18.2, JP18.2 (C)
unnamed: J19.2, JP19.2 (C)
unnamed: J20.2, JP20.2 (C)
unnamed: J21.2, JP21.2 (C)
unnamed: J22.2, JP22.2 (C)
unnamed: J23.2, JP23.2 (C)
unnamed: J24.2, JP24.2 (C)
unnamed: J25.2, JP25.2 (C)
unnamed: J26.2, JP26.2 (C)
unnamed: J27.2, JP27.2 (C)
unnamed: J28.2, JP28.2 (C)
unnamed: J29.2, JP29.2 (C)
unnamed: J30.2, JP30.2 (C)
unnamed: J31.2, JP31.2 (C)
unnamed: J32.2, JP32.2 (C)
unnamed: R9.1, U5.18 (B0)
unnamed: R10.1, U5.17 (B1)
unnamed: R11.1, U5.16 (B2)
unnamed: R12.1, U5.15 (B3)
unnamed: R13.1, U5.14 (B4)
unnamed: R14.1, U5.13 (B5)
unnamed: R15.1, U5.12 (B6)
unnamed: R16.1, U5.11 (B7)
unnamed: R17.1, U7.18 (B0)
unnamed: R18.1, U7.17 (B1)
unnamed: R19.1, U7.16 (B2)
unnamed: R20.1, U7.15 (B3)
unnamed: R21.1, U7.14 (B4)
unnamed: R22.1, U7.13 (B5)
unnamed: R23.1, U7.12 (B6)
unnamed: R24.1, U7.11 (B7)
unnamed: R25.1, U9.18 (B0)
unnamed: R26.1, U9.17 (B1)
unnamed: R27.1, U9.16 (B2)
unnamed: R28.1, U9.15 (B3)
unnamed: R29.1, U9.14 (B4)
unnamed: R30.1, U9.13 (B5)
unnamed: R31.1, U9.12 (B6)
unnamed: R32.1, U9.11 (B7)
